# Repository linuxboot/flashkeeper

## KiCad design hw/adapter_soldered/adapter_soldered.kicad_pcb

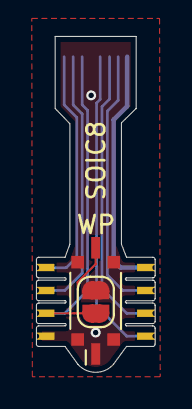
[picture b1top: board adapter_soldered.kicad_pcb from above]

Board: 2 copper layers, 6.6 x 18.7 mm, 4 parts (0 on the bottom side), 8 nets.

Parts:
J1: FFC; FFC_8_0.5mm
JP1: WP; SolderJumper-2_P1.3mm_Open_RoundedPad1.0x1.5mm
SW1: SW_DIP_x01; SW_DIP_SPSTx01_Slide_Copal_CVS-01xB_W5.9mm_P1mm
U1: SPI Flash; SolderConnector_SOIC8

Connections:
CLK: J1.6, U1.6 (CLK)
DI: J1.5, U1.5 (DI(IO0))
DO: J1.2, U1.2 (DO(IO1))
GND: J1.4, JP1.2 (B), SW1.1, SW1.3 (GND), U1.4 (GND)
VCC: J1.8, U1.8 (VCC)
/CS: J1.1, U1.1 (~CS)
/HOLD: J1.7, U1.7 (IO3)
/WP: J1.3, JP1.1 (A), SW1.2, U1.3 (IO2)
